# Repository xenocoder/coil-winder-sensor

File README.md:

Optical sensor for pickup winder

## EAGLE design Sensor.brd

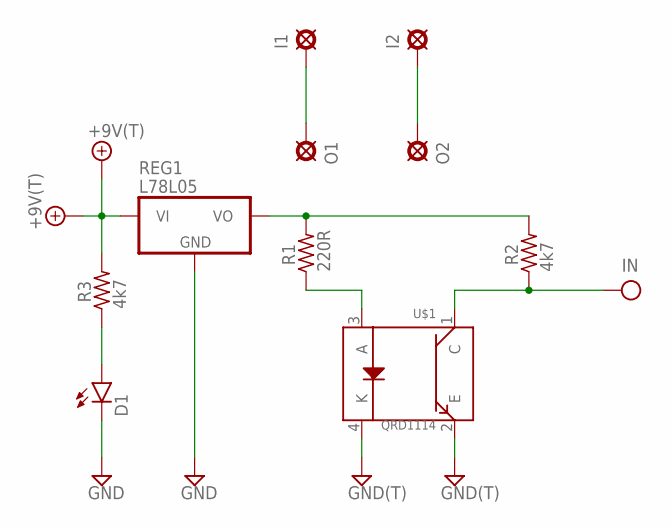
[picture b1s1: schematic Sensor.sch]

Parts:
+9V, +9V1: +9V(T); SQUARE
D1: LED3MM
G, G2: GND(T); SQUARE
I1, I2: PAD; SQUARE
IN: OUT(T); SQUARE
O1, O2: PAD; SQUARE
R1: 220R; R0207/3
R2, R3: 4k7; R0207/3
REG1: L78L05; TO92-
U$1: QRD1114

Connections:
+9V: +9V.1, +9V1.1, R3.2, REG1.1 (VI)
GND: D1.K (C), G.1, G2.1, REG1.2 (GND), U$1.2 (E), U$1.4 (K)
unnamed: R1.2, R2.2, REG1.3 (VO)
unnamed: R1.1, U$1.3 (A)
unnamed: D1.A, R3.1
unnamed: I1.1, O1.1
unnamed: I2.1, O2.1
OUT: IN.1, R2.1, U$1.1 (C)

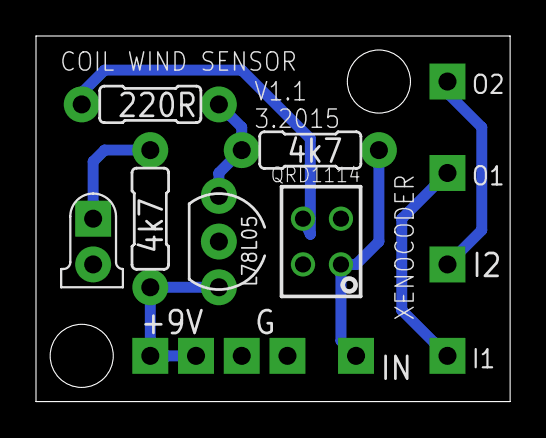
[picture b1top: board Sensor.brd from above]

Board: 2 copper layers, 26.3 x 20.3 mm, 15 parts (0 on the bottom side), 8 nets.

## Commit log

2015-10-08 Files for v1.0
